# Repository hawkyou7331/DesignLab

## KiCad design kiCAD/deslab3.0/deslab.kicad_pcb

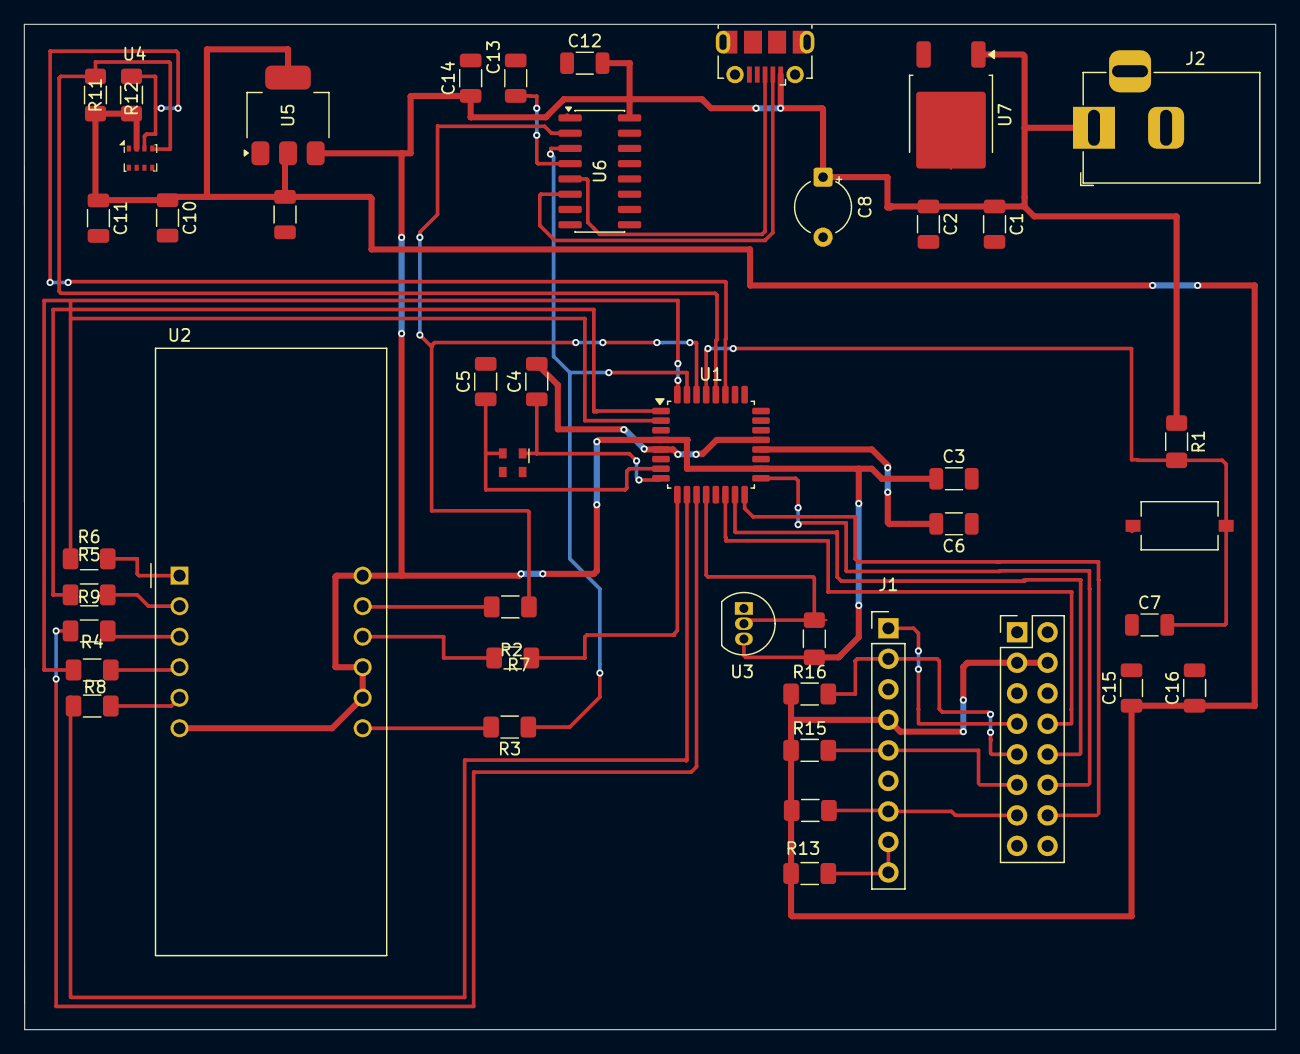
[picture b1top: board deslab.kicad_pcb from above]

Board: 2 copper layers, 104.1 x 83.7 mm, 45 parts (0 on the bottom side), 38 nets.

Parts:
C1: 0.33u; C_1206_3216Metric
C2, C9, C12, C15: 0.1u; C_1206_3216Metric
C3, C6, C7, C10, C11: 100n; C_1206_3216Metric
C4, C5: 22p; C_1206_3216Metric
C8: 10u; CP_Radial_Tantal_D4.5mm_P5.00mm
C13: 4.7u; C_1206_3216Metric
C14, C16: 10u; C_1206_3216Metric
J1: Conn_01x09; PinHeader_1x09_P2.54mm_Vertical
J2: Barrel_Jack; BarrelJack_Horizontal
J3: USB_B; USB_Micro-B_Molex-105017-0001
J4: Conn_02x08_Odd_Even; PinHeader_2x08_P2.54mm_Vertical
R1, R13, R14, R15, R16: 10k; R_1206_3216Metric_Pad1.30x1.75mm_HandSolder
R2, R3, R5, R6, R7, R8, R9: 1k; R_1206_3216Metric_Pad1.30x1.75mm_HandSolder
R4: R; R_1206_3216Metric_Pad1.30x1.75mm_HandSolder
R10, R11, R12: 4.7k; R_1206_3216Metric_Pad1.30x1.75mm_HandSolder
SW1: SW_Push; SW_Tactile_SPST_NO_Straight_CK_PTS636Sx25SMTRLFS
U1: ATmega328PB-A; TQFP-32_7x7mm_P0.8mm
U2: CC56-12GWA
U3: DS18B20; TO-92_Inline
U4: BMP280; Bosch_LGA-8_2x2.5mm_P0.65mm_ClockwisePinNumbering
U5: AMS1117-3.3; SOT-223-3_TabPin2
U6: CH340C; SOIC-16_3.9x9.9mm_P1.27mm
U7: L7805; TO-252-2
Y1: Crystal; Oscillator_SMD_Abracon_ASDMB-4Pin_2.5x2.0mm

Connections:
+3.3V: C9.2, C10.1, C11.1, C15.1, C16.1, J1.4, J4.3, J4.4, R11.2, R12.1, R13.1, R14.1, R15.1, R16.1, U4.2 (CSB), U4.6 (VDDIO), U4.8 (VDD), U5.2 (VO)
+5V: C1.1, C2.1, C3.1, C8.1, C12.2, C14.1, J2.1, J3.1 (VBUS), R1.1, R10.2, U1.4 (VCC), U1.18 (AVCC), U2.6 (CC4), U2.8 (CC3), U2.9 (CC2), U2.12 (CC1), U3.3 (V_{DD}), U5.3 (VI), U6.16 (VCC), U7.1 (IN), U7.3 (OUT)
AREF: C6.2, U1.20 (AREF)
D+: J3.3 (D+), U6.5 (UD+)
D-: J3.2 (D-), U6.6 (UD-)
GND: C1.2, C2.2, C3.2, C4.2, C5.2, C6.1, C7.1, C8.2, C9.1, C10.2, C11.2, C12.1, C13.2, C14.2, C15.2, C16.2, J1.3, J1.6, J2.2, J3.4 (GND), J3.5 (Shield), J4.1, J4.2, J4.15, J4.16, SW1.1, U1.5 (GND), U1.21 (GND), U3.1 (GND), U4.1 (GND), U4.5 (SDO), U4.7 (GND), U5.1 (GND), U6.1 (GND), U7.2 (GND)
MISO: J1.7, J4.13, R14.2
MOSI: J1.2, J4.9, R16.2
unnamed: J1.8, J1.9, R13.2
unnamed: C5.1, U1.7 (XTAL1/PB6), Y1.2
unnamed: C4.1, U1.8 (XTAL2/PB7), Y1.1
unnamed: R9.2, U2.3 (DPX)
unnamed: R2.2, U2.11 (a)
unnamed: R3.2, U2.7 (b)
unnamed: R4.2, U2.4 (c)
unnamed: R5.2, U2.2 (d)
unnamed: R6.2, U2.1 (e)
unnamed: R7.2, U2.10 (f)
unnamed: R8.2, U2.5 (g)
unnamed: C13.1, U6.4 (V3)
PB0: R10.1, U1.12 (PB0), U3.2 (DQ)
PB2: J4.8, U1.14 (PB2)
PB3: J4.10, U1.15 (PB3)
PB4: J4.14, U1.16 (PB4)
PB5: J4.12, U1.17 (PB5)
PC4: R12.2, U1.27 (PC4), U4.3 (SDI)
PC5: R11.1, U1.28 (PC5), U4.4 (SCK)
PD2: R4.1, U1.32 (PD2)
PD3: R5.1, U1.1 (PD3)
PD4: R6.1, U1.2 (PD4)
PD5: R7.1, U1.9 (PD5)
PD6: R8.1, U1.10 (PD6)
PD7: R9.1, U1.11 (PD7)
RESET: C7.2, R1.2, SW1.2, U1.29 (~RESET/PC6)
RX/PD0: R2.1, U1.30 (PD0), U6.2 (TXD)
SCK: J1.5, J4.11, R15.2
SDCS: J1.1, J4.7
TX/PD1: R3.1, U1.31 (PD1), U6.3 (RXD)

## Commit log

2025-10-29 Create d
2025-10-29 Rename CH340DS1.pdf to datasheets/CH340DS1.pdf
2025-10-29 Rename DS_FT232R.pdf to datasheets/DS_FT232R.pdf
2025-10-29 Rename TEMT6000.pdf to datasheets/TEMT6000.pdf
2025-10-29 Rename bst-bmp280-ds001.pdf to datasheets/bst-bmp280-ds001.pdf
2025-10-29 Rename ds18b20.pdf to datasheets/ds18b20.pdf
2025-10-29 Rename eone-1602a1.pdf to datasheets/eone-1602a1.pdf
2025-10-29 Rename mpu6050_6_dof_accelerometer_and_gyro-2489019.pdf to datasheets/mpu6050_6_dof_accelerometer_and_gyro-2489019.pdf
2025-11-05 Create kiCAD2
2025-11-05 Rename des_lab.kicad_pcb to kiCAD/kiCAD2_0/des_lab.kicad_pcb
2025-11-05 Rename des_lab.kicad_prl to kiCAD/kiCAD2_0/des_lab.kicad_prl
2025-11-05 Rename des_lab.kicad_pro to kiCAD/kiCAD2_0/des_lab.kicad_pro
2026-01-22 Create R
